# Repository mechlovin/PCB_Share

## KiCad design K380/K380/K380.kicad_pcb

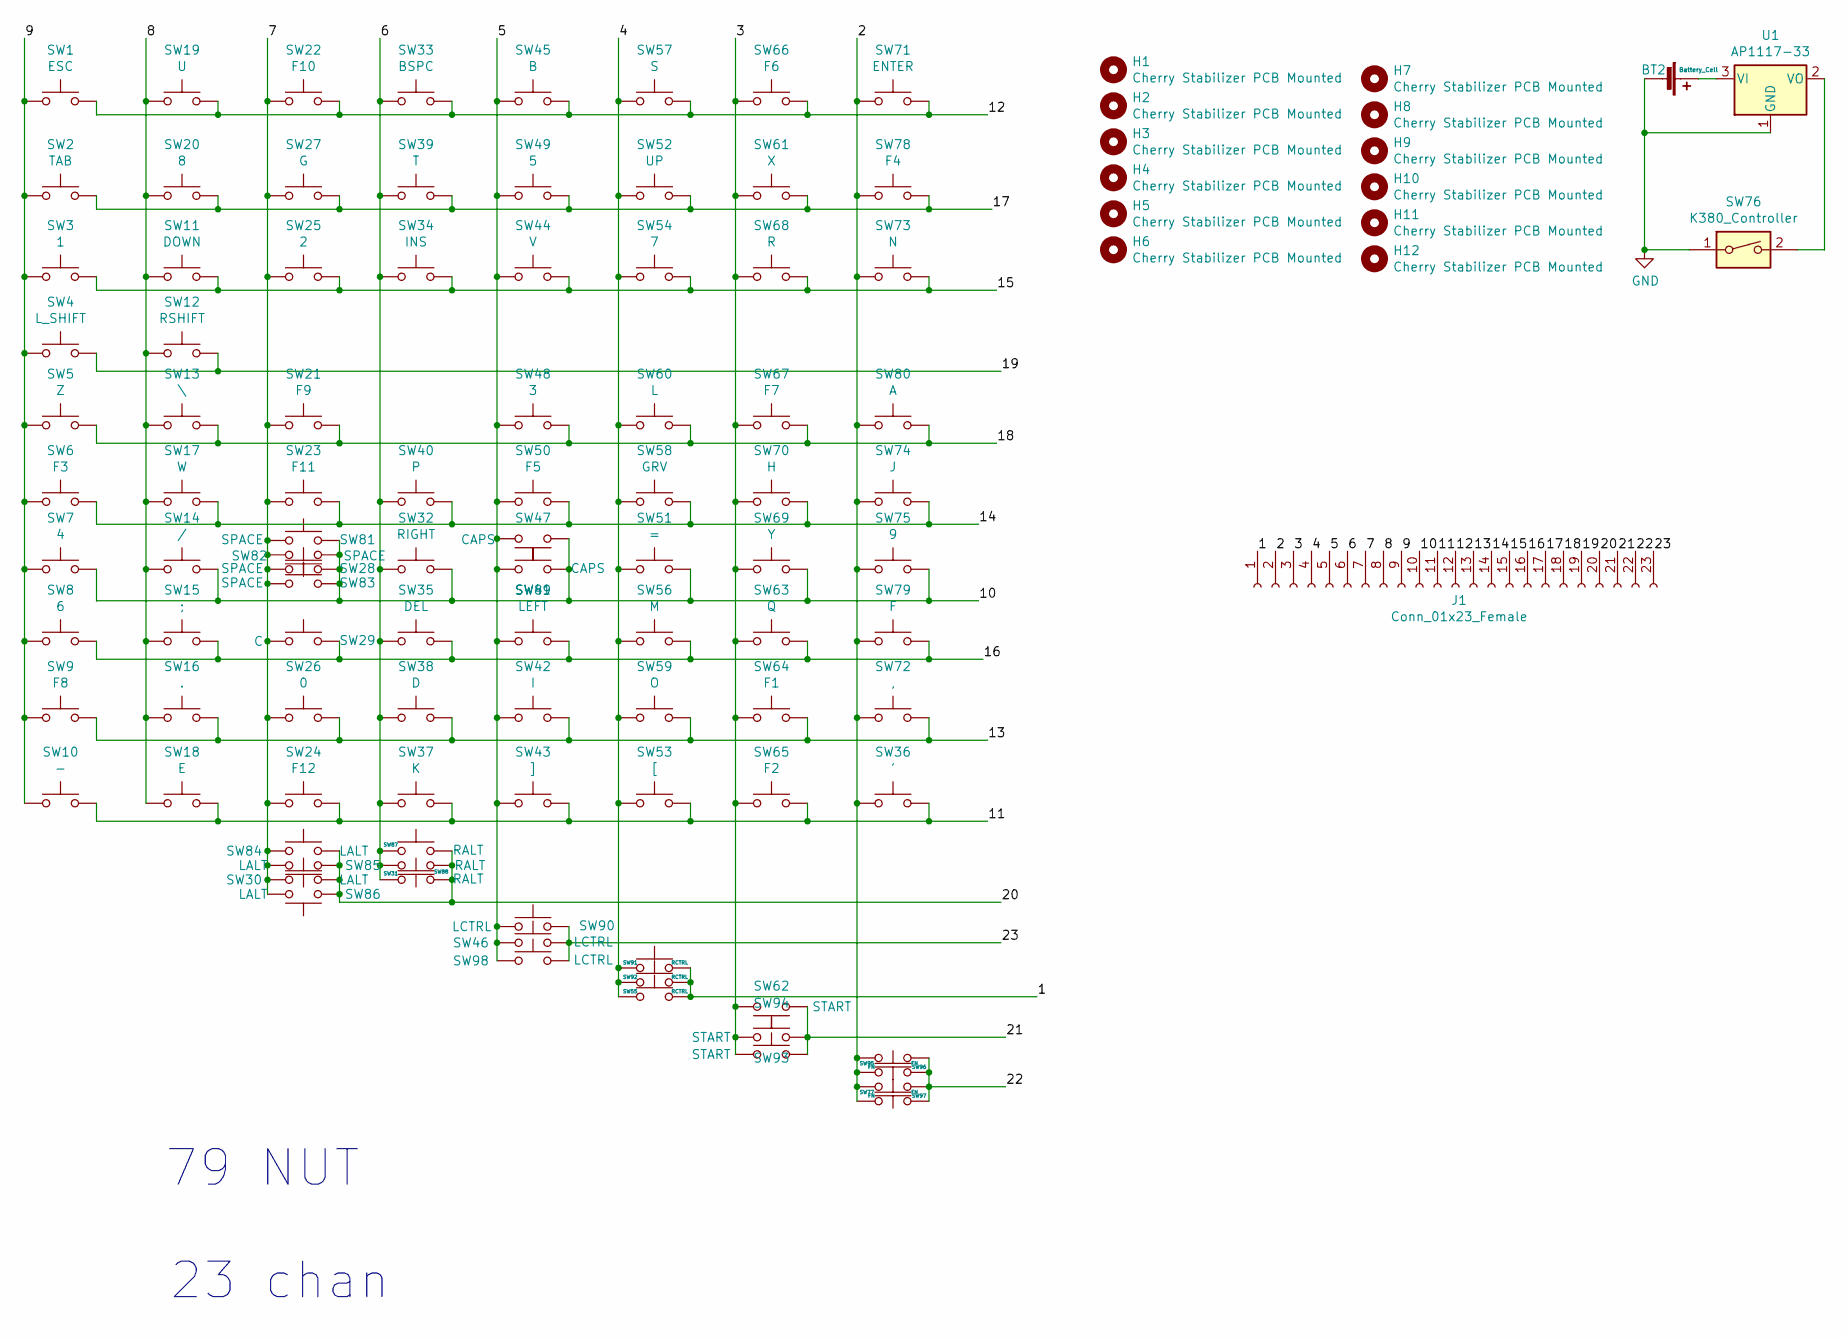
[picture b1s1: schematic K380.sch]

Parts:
BT2: Battery_Cell; BatteryHolder_Keystone_1060_1x2032
H1, H2, H3, H4, H5, H6, H7, H8, H9, H10, H11, H12: Cherry Stabilizer PCB Mounted; Cherry_Stab_PCBMounted
J1: Conn_01x23_Female; Molex_200528-0230_1x23-1MP_P1.00mm_Horizontal
SW1: ESC; CHERRY_PCB_100H_Thermal
SW2: TAB; CHERRY_PCB_100H_Thermal
SW3: 1; CHERRY_PCB_100H_Thermal
SW4: L_SHIFT; CHERRY_PCB_100H_Thermal
SW5: Z; CHERRY_PCB_100H_Thermal
SW6: F3; CHERRY_PCB_100H_Thermal
SW7: 4; CHERRY_PCB_100H_Thermal
SW8: 6; CHERRY_PCB_100H_Thermal
SW9: F8; CHERRY_PCB_100H_Thermal
SW10: -; CHERRY_PCB_100H_Thermal
SW11: DOWN; CHERRY_PCB_100H_Thermal
SW12: RSHIFT; CHERRY_PCB_100H_Thermal
SW13: \\; CHERRY_PCB_100H_Thermal
SW14: /; CHERRY_PCB_100H_Thermal
SW15: ;; CHERRY_PCB_100H_Thermal
SW16: .; CHERRY_PCB_100H_Thermal
SW17: W; CHERRY_PCB_100H_Thermal
SW18: E; CHERRY_PCB_100H_Thermal
SW19: U; CHERRY_PCB_100H_Thermal
SW20: 8; CHERRY_PCB_100H_Thermal
SW21: F9; CHERRY_PCB_100H_Thermal
SW22: F10; CHERRY_PCB_100H_Thermal
SW23: F11; CHERRY_PCB_100H_Thermal
SW24: F12; CHERRY_PCB_100H_Thermal
SW25: 2; CHERRY_PCB_100H_Thermal
SW26: 0; CHERRY_PCB_100H_Thermal
SW27: G; CHERRY_PCB_100H_Thermal
SW28, SW81, SW82, SW83: SPACE; CHERRY_PCB_100H_Thermal
SW29: C; CHERRY_PCB_100H_Thermal
SW30, SW84, SW85, SW86: LALT; CHERRY_PCB_100H_Thermal
SW31, SW87, SW88: RALT; CHERRY_PCB_100H_Thermal
SW32: RIGHT; CHERRY_PCB_100H_Thermal
SW33: BSPC; CHERRY_PCB_100H_Thermal
SW34: INS; CHERRY_PCB_100H_Thermal
SW35: DEL; CHERRY_PCB_100H_Thermal
SW36: '; CHERRY_PCB_100H_Thermal
SW37: K; CHERRY_PCB_100H_Thermal
SW38: D; CHERRY_PCB_100H_Thermal
SW39: T; CHERRY_PCB_100H_Thermal
SW40: P; CHERRY_PCB_100H_Thermal
SW41: LEFT; CHERRY_PCB_100H_Thermal
SW42: I; CHERRY_PCB_100H_Thermal
SW43: ]; CHERRY_PCB_100H_Thermal
SW44: V; CHERRY_PCB_100H_Thermal
SW45: B; CHERRY_PCB_100H_Thermal
SW46, SW90, SW98: LCTRL; CHERRY_PCB_100H_Thermal
SW47, SW89: CAPS; CHERRY_PCB_100H_Thermal
SW48: 3; CHERRY_PCB_100H_Thermal
SW49: 5; CHERRY_PCB_100H_Thermal
SW50: F5; CHERRY_PCB_100H_Thermal
SW51: =; CHERRY_PCB_100H_Thermal
SW52: UP; CHERRY_PCB_100H_Thermal
SW53: [; CHERRY_PCB_100H_Thermal
SW54: 7; CHERRY_PCB_100H_Thermal
SW55, SW91, SW92: RCTRL; CHERRY_PCB_100H_Thermal
SW56: M; CHERRY_PCB_100H_Thermal
SW57: S; CHERRY_PCB_100H_Thermal
SW58: GRV; CHERRY_PCB_100H_Thermal
SW59: O; CHERRY_PCB_100H_Thermal
SW60: L; CHERRY_PCB_100H_Thermal
SW61: X; CHERRY_PCB_100H_Thermal
SW62, SW93, SW94: START; CHERRY_PCB_100H_Thermal
SW63: Q; CHERRY_PCB_100H_Thermal
SW64: F1; CHERRY_PCB_100H_Thermal
SW65: F2; CHERRY_PCB_100H_Thermal
SW66: F6; CHERRY_PCB_100H_Thermal
SW67: F7; CHERRY_PCB_100H_Thermal
SW68: R; CHERRY_PCB_100H_Thermal
SW69: Y; CHERRY_PCB_100H_Thermal
SW70: H; CHERRY_PCB_100H_Thermal
SW71: ENTER; CHERRY_PCB_100H_Thermal
SW72: ,; CHERRY_PCB_100H_Thermal
SW73: N; CHERRY_PCB_100H_Thermal
SW74: J; CHERRY_PCB_100H_Thermal
SW75: 9; CHERRY_PCB_100H_Thermal
SW76: K380_Controller
SW77, SW95, SW96, SW97: FN; CHERRY_PCB_100H_Thermal
SW78: F4; CHERRY_PCB_100H_Thermal
SW79: F; CHERRY_PCB_100H_Thermal
SW80: A; CHERRY_PCB_100H_Thermal
U1: AP1117-33; SOT-223-3_TabPin2

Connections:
/1: J1.1, SW55.2, SW91.2, SW92.2
/2: J1.2, SW36.1, SW71.1, SW72.1, SW73.1, SW74.1, SW75.1, SW77.2, SW78.1, SW79.1, SW80.1, SW95.2, SW96.1, SW97.1
/3: J1.3, SW61.1, SW62.1, SW63.1, SW64.1, SW65.1, SW66.1, SW67.1, SW68.1, SW69.1, SW70.1, SW93.2, SW94.1
/4: J1.4, SW51.1, SW52.1, SW53.1, SW54.1, SW55.1, SW56.1, SW57.1, SW58.1, SW59.1, SW60.1, SW91.1, SW92.1
/5: J1.5, SW41.1, SW42.1, SW43.1, SW44.1, SW45.1, SW46.1, SW47.1, SW48.1, SW49.1, SW50.1, SW89.2, SW90.1, SW98.1
/6: J1.6, SW31.1, SW32.1, SW33.1, SW34.1, SW35.1, SW37.1, SW38.1, SW39.1, SW40.1, SW87.1, SW88.2
/7: J1.7, SW21.1, SW22.1, SW23.1, SW24.1, SW25.1, SW26.1, SW27.1, SW28.1, SW29.1, SW30.1, SW81.1, SW82.2, SW83.1, SW84.1, SW85.2, SW86.2
/8: J1.8, SW11.1, SW12.1, SW13.1, SW14.1, SW15.1, SW16.1, SW17.1, SW18.1, SW19.1, SW20.1
/9: J1.9, SW1.1, SW2.1, SW3.1, SW4.1, SW5.1, SW6.1, SW7.1, SW8.1, SW9.1, SW10.1
/10: J1.10, SW7.2, SW14.2, SW28.2, SW32.2, SW47.2, SW51.2, SW69.2, SW75.2, SW81.2, SW82.1, SW83.2, SW89.1
/11: J1.11, SW10.2, SW18.2, SW24.2, SW36.2, SW37.2, SW43.2, SW53.2, SW65.2
/12: J1.12, SW1.2, SW19.2, SW22.2, SW33.2, SW45.2, SW57.2, SW66.2, SW71.2
/13: J1.13, SW9.2, SW16.2, SW26.2, SW38.2, SW42.2, SW59.2, SW64.2, SW72.2
/14: J1.14, SW6.2, SW17.2, SW23.2, SW40.2, SW50.2, SW58.2, SW70.2, SW74.2
/15: J1.15, SW3.2, SW11.2, SW25.2, SW34.2, SW44.2, SW54.2, SW68.2, SW73.2
/16: J1.16, SW8.2, SW15.2, SW29.2, SW35.2, SW41.2, SW56.2, SW63.2, SW79.2
/17: J1.17, SW2.2, SW20.2, SW27.2, SW39.2, SW49.2, SW52.2, SW61.2, SW78.2
/18: J1.18, SW5.2, SW13.2, SW21.2, SW48.2, SW60.2, SW67.2, SW80.2
/19: J1.19, SW4.2, SW12.2
/20: J1.20, SW30.2, SW31.2, SW84.2, SW85.1, SW86.1, SW87.2, SW88.1
/21: J1.21, SW62.2, SW93.1, SW94.2
/22: J1.22, SW77.1, SW95.1, SW96.2, SW97.2
/23: J1.23, SW46.2, SW90.2, SW98.2
GND: BT2.2 (-), SW76.1, U1.1 (GND)
unnamed: BT2.1 (+), U1.3 (VI)
unnamed: SW76.2, U1.2 (VO)

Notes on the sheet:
79 NUT
23 chan

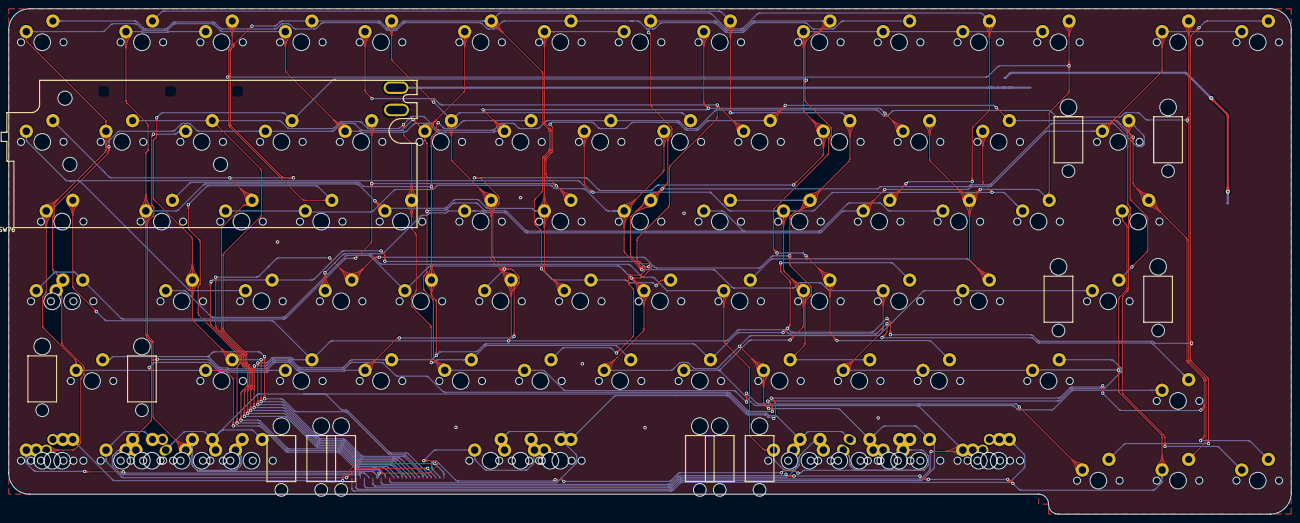
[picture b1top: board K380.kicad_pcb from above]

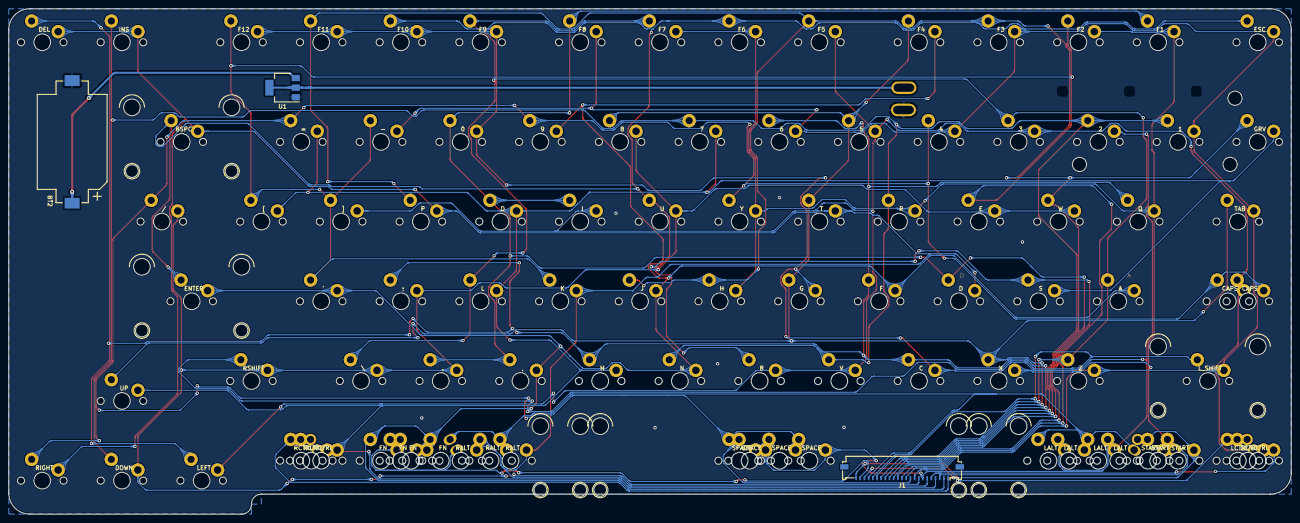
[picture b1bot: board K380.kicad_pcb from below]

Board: 2 copper layers, 306.5 x 120.8 mm, 113 parts (3 on the bottom side), 26 nets.

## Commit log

2020-04-23 Tạo mới phím dùng bộ điều khiển K380
    Phím 75% dùng mạch điều khiển của Logitech K380
2020-04-23 xóa file không cần thiết
